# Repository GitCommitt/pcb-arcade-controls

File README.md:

# README: pcb-arcade-controls

# Planning: 
**Periode:** November 2026 t/m januari 2027

---

### Sprint 0
* **Periode:** 16 nov t/m 20 nov 2026
* **Taken:** 
  * Onderzoek / start

### Sprint 1
* **Periode:** 23 nov t/m 4 dec 2026
* **Taken:** 
  * Stroomschema ontwerpen

### Sprint 2
* **Periode:** 7 dec t/m 18 dec 2026
* **Taken:** 
  * Printplaat ontwerpen
  * Printplaten bestellen

### Kerstvakantie
* **Periode:** 21 dec 2026 t/m 1 jan 2027
* **Status:** Geen sprint

### Sprint 3
* **Periode:** 4 jan t/m 15 jan 2027
* **Taken:** 
  * Firmware & software
  * Handleidingen & solderen

### Sprint 4
* **Periode:** 18 jan t/m 22 jan 2027
* **Taken:** 
  * Polishen
  * CGI's
    
## Onderzoek

Bij het onderzoek zijn we begonnen met de PDF lezen en belangerijke dingen opslaan. We hebben aan het begin van dit process een [video](https://www.youtube.com/watch?v=8WXpGTIbxlQ) gekeken hoe we het software tool KiCad moeten gebruiken in combinatie met de STM32F072CBT6 Microprocessor.

### Keuze pins

Daan en Bram zijn gaan onderzoeken welke pins er gebruikt kunnen worden op de processor en kijken hoe we uitkkomen met de aantal connecties die we hebben door de connectors. Samen zijn we er uit gekomen dat het handig is om een matrix te gebruiken voor de connector connections naar de processor. We waren in de [datasheet](https://www.lcsc.com/datasheet/C81720.pdf) gedoken. Hier ijn we op pagina 35 onder het kopje (Pinouts and pin descriptions) onder wij gebruiken de pin number (LQFP48). Heir hebben we de pins uitgezocht welke we kunnen gebruiken.

## Kicad

In Kicad zijn we begonnen bij het maken van een nieuwe file met de template [library](https://github.com/GitCommitt/pcb-arcade-controls/tree/main/library/scottokeebs-main/Extras/ScottoModules/STM32F072CBT6) van de repo [Scottokeebs](https://github.com/joe-scotto/scottokeebs). Daarna hebben we voor het maken van een 3d model de [library](https://github.com/GitCommitt/pcb-arcade-controls/tree/main/library/scottokeebs-main/Extras/ScottoKicad/symbols) toegevoed aan onze preferences. 14

## Pin Layout

Hieronder staan de pins die we gebruiken in het project. Hier hebben Daan en Fynn samen onderzocht.

### Matrix, Kolommen & Rijen
| Pin | Functie | MCU Pin |
| :--- | :--- | :--- |
| **14** | Col 0 | `PA4` |
| **15** | Col 1 | `PA5` |
| **16** | Col 2 | `PA6` |
| **17** | Col 3 | `PA7` |
| **18** | Col 4 | `PB0` |
| **19** | Col 5 | `PB1` |
| **20** | Col 6 | `PB2` |
| **21** | Col 7 | `PB10` |
| **22** | Row 0 | `PB11` |
| **25** | Row 1 | `PB12` |
| **26** | Row 2 | `PB13` |
| **27** | Row 3 | `PB14` |

### Power & GND
| Pin | Functie | MCU Pin |
| :--- | :--- | :--- |
| **1** | VBAT | `VBAT` |
| **9** | VDDA | `VDDA` |
| **24** | VDD1 | `VDD` |
| **36** | VDDIO2 | `VDDIO2` |
| **48** | VDD2 | `VDD` |
| **8** | GND | `VSSA` |
| **23** | GND | `VSS` |

### USB & Debugging
| Pin | Functie | MCU Pin |
| :--- | :--- | :--- |
| **32** | USB_D- | `PA11` |
| **33** | USB_D+ | `PA12` |
| **34** | A13 | `PA13` |
| **37** | A14 | `PA14` |

### Systeem & Overige I/O
| Pin | Functie | MCU Pin |
| :--- | :--- | :--- |
| **2** | C13 | `PC13` |
| **3** | C14 | `PC14` |
| **4** | C15 | `PC15` |
| **7** | NRST | `NRST` |
| **28** | B15 | `PB15` |
| **44** | BOOT0 | `BOOT0` |

# Connector type

**PCB Connector**

Daan heeft voor de [JST-XH Female](https://nl.rs-online.com/web/p/pcb-headers/8201554) connectors gekozen als connectie type. Daan heeft deze keuze gemaakt aangezien deze type connector makkelijk is om te gebruiken en super gebruiksvriendelijk is. Ook was een reden dat Daan deze connectie type heeft gekozen dat deze connectors makkelijk op het bord passen en niet veel plek in beslag nemen op de printplaat. De andere connectie type die Daan als optie had waren de [Screw Terminals](https://www.amazon.nl/-/en/50pcs-Terminal-Connectors-Terminals-2-54mm/dp/B07BVF8MD1). Het voordeel bij deze connector was vooral dat hij universal is dus elke soort kabel kan gebruikt worden op deze connector. Daan heeft alleen niet voor deze connector gekozen om de volgende redenen. De connectors nemen veel plek in beslag op de printplaat en de connectors niet gebruiksvriendlijk aangezien je voor het veranderen van de kabel een schroevendraaier nodig heb.

**Kabel Connector**

We gaan voor de kabel connectors aan de pcb kant de [JST XH-2 Male](https://www.electrokit.com/en/batterisladd-jst-xh-2-pol-300mm) connectors gebruiken. Deze connectors passen perfect in de female connectors van de pcb. Als deze twee connectors zijn gekoppeld zijn ze moeilijk uit te halen en zullen ze dus niet uitvallen tijdens het gebruik. 

Aan de ardcade button kant van de kabel gaan we de [Quick-Connect](https://www.arcadewinkel.nl/en/wiring-connectors/connectors/quick-connector-2-8mm-110-inch-crimp-model-10pcs) connectors gebruiken aangezien deze makkelijk hot swapable zijn met de arcade buttons en dus ook heel gebruiksvriendelijk zijn voor de gebruikers als er word gewisseld van buttons.

De kabel die het uiteindelijk gaan worden zijn de [JST XH male / Quick-Connect Wires](https://www.amazon.nl/SJ-JX-Connectors-Controller-Accessories/dp/B08C2CLMJ5?th=1). Dit omdat deze het beste bij onze keuzes het beste passen en gaan werken in ons ontwerp.

## Matrix

Wij gaan een matrix gebruiken in ons prinplaat ontwerp, aangezien dit super handig en overzichtelijk is voor het pin gebruik van de pins op de processor. De matrix houd in dat de data en ground pins van de connectors worden samengevoegd zogeheten een matrix. Hierdoor hebben we inplaats van 24 pins maar 10 pins nodig. De verhouding van de matrix is 4 x 6 dat zijn dus 4 rows en 6 columns. Hierdoor hebben wij dus meer mogelijkheden om andere dingen toe te voegen zoals een led strip of andere componenten.

# Process

We zijn begonnen als een team met het bedenken van een strak plan om dit project zo goed en het soepelst mogelijk kan laten verlopen. We zijn eerst begonnen met de verdeling van de taken. In de PCB ontwerp periode zijn de volgende taken verdeelt. Fynn, Nathan en Kevin hebben de taken gekregen van het PCB ontwerp te creeren en dan ook gelijk in Kicad te verwerken. Daan en Bram hebben de taak gekregen om te kijken wat de beste opties zijn voor het gebruik van de pins. Hiermee word bedoeld van welke pins op de processor gebruikt worden voor data zodat het knoppen en joysticks goed gaan comminuceren met de processor. 

## Sprint 0 [↗️](https://github.com/GitCommitt/pcb-arcade-controls/tree/main/attachments/sprints/sprint-0)

### Doelen

...

### Aanpak
We hebben als eerst met het gehele team gekeken naar hoe het programma Kicad in elkaar zit en hoe we dit kunnen gaan gebruiken om de PCB uiteindelijk te kunnen ontwerpen. Er is ook een vergadering plaatsgevonden met het team waarbij we alles wat we hebben bij elkaar hebben gelegd om op die manier te meten waar we in het process staan. Wij hebben hiervoor ook ene duidelijke [planning](https://github.com/GitCommitt/pcb-arcade-controls/blob/main/README.md#planning) gemaakt voor wanneer welke taak afgerond moet zijn zodat we goed op schema blijven liggen. 

Samen met z'n allen is er een design ontworpen hoe het schema er op dit moment uit ziet ([Bekijk](https://github.com/GitCommitt/pcb-arcade-controls/blob/main/attachments/sprints/sprint-0/schema.png)). Hier zijn de PCB ontwerpers bezig geweest met het bouwen van de basis, dus er is op het schema te zien dat de benodigde connectors, processor, bootloaderknop en usb c port zijn toegevoegd. Later in het process/andere sprints zal er waarschijnlijk gebruik worden gemaakt van een matrix waardoor er nog meer connectors aangesloten kunnen worden en er daardoor meer controls zijn.

Het schema is ook al verwerkt in een visuele printplaat ontwerp ([Bekijk](https://github.com/GitCommitt/pcb-arcade-controls/blob/main/attachments/sprints/sprint-0/pcb.png)). Op dit ontwerp is te zien dat we 24 inputconnectoren gebruiken die we later gaan vervangen voor nieuwe connectors. Dat zijn de [JST-XH connectors](https://nl.rs-online.com/web/p/pcb-headers/8201554). Ook is er op de printplaat al nagedacht over hoe de printplaat gemonteerd kan worden aan een spelkast of ander iets. Hiervoor zijn 4 montagegaten van 10 mm gemaakt in de printplaat en worden waarschijnlijk later in het process smaller gemaakt zodat ze perfect bevestigd kunnen worden met een schroefjes. De processor, bootloaderknop en usb-c aansluiting zijn op dit ontwerp mogelijk op andere plekken dan ze op het eindproduct zouden zitten.

We hebben een presentatie gemaakt die deze sprint samenvat in 5 dia's ([Bekijk](https://github.com/GitCommitt/pcb-arcade-controls/blob/main/attachments/sprints/sprint-0/Presentatie%20sprint0.pptx)). Dit hebben we gepresenteerd en hebben we ook [feedback](https://github.com/GitCommitt/pcb-arcade-controls/blob/main/attachments/sprints/sprint-0/Resultaatfeedback%20presentative.txt) op gekregen en verwerkt.

## Sprint 1 [↗️](https://github.com/GitCommitt/pcb-arcade-controls/tree/main/attachments/sprints/sprint-1)

### Doelen [↗️](https://github.com/GitCommitt/pcb-arcade-controls/blob/main/attachments/sprints/sprint-1/Doel-sprint%201.docx)
Voor sprint 1 willen we ervoor zorgen dat we meer te weten komen hoe we moeten designen in kicad en hoe we alles kunnen toevoegen, zoals connectoren zoeken, processor importeren uit een bestaand project van andere. Ook moet er een begin gemaakt worden in kicad. De basis staat. Onder de basis valt uiteraard het ontwerpen van de pcb. 

De printplaat moet de volgende eisen hebben gehaald aan het einde van de week. De eerste eis is dat er een pcb moet staan die op maat is van de uiteindelijke printplaat. Hierdoor kunnen we zien hoeveel ruimte we hebben om te werken met de componenten die later worden toevoegt. De volgende eis is dat we de processor moeten vinden en die ook toevoegen in het project en uiteindelijk ook op die printplaat laat zetten. Hierbij hoort ook de bootknop, deze is cruciaal omdat door deze knop kunnen we firmware gaan zetten op de processor en het ook werkend kunnen laten maken. Ook moet de USB C port aanwezig zijn in het schematic en ook al op de printplaat fysiek zit. 

### Aanpak

Kevin is begonnen met het onderzoeken van hoe er samen in 1 KiCad bestand gewerkt kan worden zonder dat het elkaar constant over overschrijft. Dit is onderzocht en er kwam een stappenlijst uit. Het volgende is gedaan om dit probleem op te lossen: in KiCad is bij de voorkeuren git versie beheer ingeschakeld. Hierdoor overschrijven de bestanden niet meer waardoor er nu met meerdere personen aan 1 bestand gewerkt kan worden. Kevin heeft dit gedaan en werd hierbij geholpen door Daan, Nathan en Fynn.

Daan en Bram hebben ook het onderzoek gestart naar het kijken welke ADC connecties gebruikt kunnen worden van de processor voor de data en de ground connecties van de buttons ([Bekijk](https://github.com/GitCommitt/pcb-arcade-controls/blob/main/attachments/sprints/sprint-1/PINoutSchematic.txt)).

Het PCB ontwerp en de schematic worden nu aangepast en worden de temporary pins die nu gebruikt worden door de buttons opnieuw aan een pin gezet. Er word gewerkt aan het erin zetten van de processor op de pcb aangezien die nu niet word weergegeven bij de pcb. Nathan heeft de connectors toegevoegd en dus zijn de connectors die daadwerkelijk gebruikt gaan worden zichtbaar op de [pcb](https://github.com/GitCommitt/pcb-arcade-controls/blob/main/attachments/sprints/sprint-1/pcb.png). Hierdoor is er een beter zicht over hoe de pin lay-out eruit gaat zien en hoe de connectors op de pcb komen. [De pin layout](https://github.com/GitCommitt/pcb-arcade-controls/blob/main/attachments/sprints/sprint-1/PINoutSchematic.txt) is ook gecreerd waardoor er nu duidelijk gemaakt waar de pins heen gaan op de processor.

Kevin heeft de processor toegevoegd aan het [pcb design](https://github.com/GitCommitt/pcb-arcade-controls/blob/main/attachments/sprints/sprint-1/pcb-2.png) en deze is nu zichtbaar. De pins van de connectors moeten nog verbonden worden aan de processor alleen staat hij er voor nu wel alvast op de pcb en kunnen deze later aan elkaar verbonden worden voor een beter zicht op hoe de pcb gaat werken. De processor is uit de KiCad library gehaald en er was dus geen externe footprint voor nodig waardoor het ook makkelijker maakt voor op GitHub te zetten en samen te werken. 

Fynn heeft een nieuw [schematic](https://github.com/GitCommitt/pcb-arcade-controls/blob/main/attachments/sprints/sprint-1/schematic.png) gemaakt voor de connectors. Nu is er te vinden welke connectors bij welke column en row horen. hierdoor is het makkelijk te achterhalen welke connector waar heen moet. Ook zijn er nieuwe labels toegevoegd zoals player-1-button-1 etc etc. Ook is er toegevoegd in de [schematic](https://github.com/GitCommitt/pcb-arcade-controls/blob/main/attachments/sprints/sprint-1/schematic.png) welke diodes Fynn gebruikt voor de matrix. Op de prinplaat zijn ondertussen nieuwe [traces](https://github.com/GitCommitt/pcb-arcade-controls/blob/main/attachments/sprints/sprint-1/pcb-3.png) gelegd dat is op de fotos te zien van het 3d model.

Nathan heeft gewerkt aan het de gaten die in de printplaat komen. Hij is ervoor gaan zorgen dat hij bestel ready word. Hierdoor kunnen we uiteindelijk zelf de componenten gaan solderen aangezien het onnodig is om elke component erop te laten solderen door de fabriek. Alleen de capacitors en de MCU (processor) is blijven zitten aangezien deze componenten te klein zijn om die met de hand te solderen ([Bekijk](https://github.com/GitCommitt/pcb-arcade-controls/blob/main/attachments/sprints/sprint-1/pcb-holes.png)).

Kevin heeft de connecties van PA11 en PA12 die eerst MCU_D- en MCU_D+ waren nu veranderd naar USB_D- en USB_D+. Dit omdat dit overeenkomt met de USB C connector die we gebruiken op de printplaat. Dit is ook aangepast op het schematic [(Bekijk)](https://github.com/GitCommitt/pcb-arcade-controls/blob/main/attachments/sprints/sprint-1/schematic-usb_update.png). De traces van J3 naar U4 zijn beter geroute waardoor het nu er netter eruit ziet.

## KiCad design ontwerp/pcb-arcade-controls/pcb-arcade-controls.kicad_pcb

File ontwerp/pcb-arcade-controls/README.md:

# README: pcb-arcade-controls

**Onderzoek**
---

Bij het onderzoek zijn we begonnen met de PDF lezen en belangerijke dingen opslaan. We hebben aan het begin van dit process een [video](https://www.youtube.com/watch?v=8WXpGTIbxlQ) gekeken hoe we het software tool KiCad moeten gebruiken in combinatie met de STM32F072CBT6 Microprocessor.

## Kicad

In Kicad zijn we begonnen bij het maken van een nieuwe file met de template [library](https://github.com/GitCommitt/pcb-arcade-controls/tree/main/library/scottokeebs-main/Extras/ScottoModules/STM32F072CBT6) van de repo [Scottokeebs](https://github.com/joe-scotto/scottokeebs). Daarna hebben we voor het maken van een 3d model de [library](https://github.com/GitCommitt/pcb-arcade-controls/tree/main/library/scottokeebs-main/Extras/ScottoKicad/symbols) toegevoed aan onze preferences.

# Meeting 6 november 2026
- Externe power supply voor de led strip (omdat er anders dubbele volt op komt)

- ADC onderzoek nog doen (verder afmaken), (datasheets induiken, qmk adc (link naar tbos) adc pins zijn data pins maar niet allemaal)

-   pa0 tot pa15 ADC pins (dubbelchecken) qmk adc link checken

- page 35 datasheet (lscs.com/datasheet/C91720.pdf)

- form factor is LQFP48 

- ADC kan je het analog uitlezen

- op de sheet kijken welke pin werken

- niet naar de grotere versies kijken

- goed kijken welke ze hebben en welke je kan aansluiten (bij de datasheet)

- Eerst ADC pins klaar zetten en dan pas de rest

- Readme is voor alles

- Presentatie maken maandag 16 nov (daarbij de debriefing, taakverdeling, planning)

------

## Sprint meeting 0

Resultaat/feedback presentative:

- Alles ziet er goed uit ivm connectoren etc
- nu is het 0 punt en weten wat we moeten doen
- letten op documentatie, alles documenteren al is het iets kleins/simpel

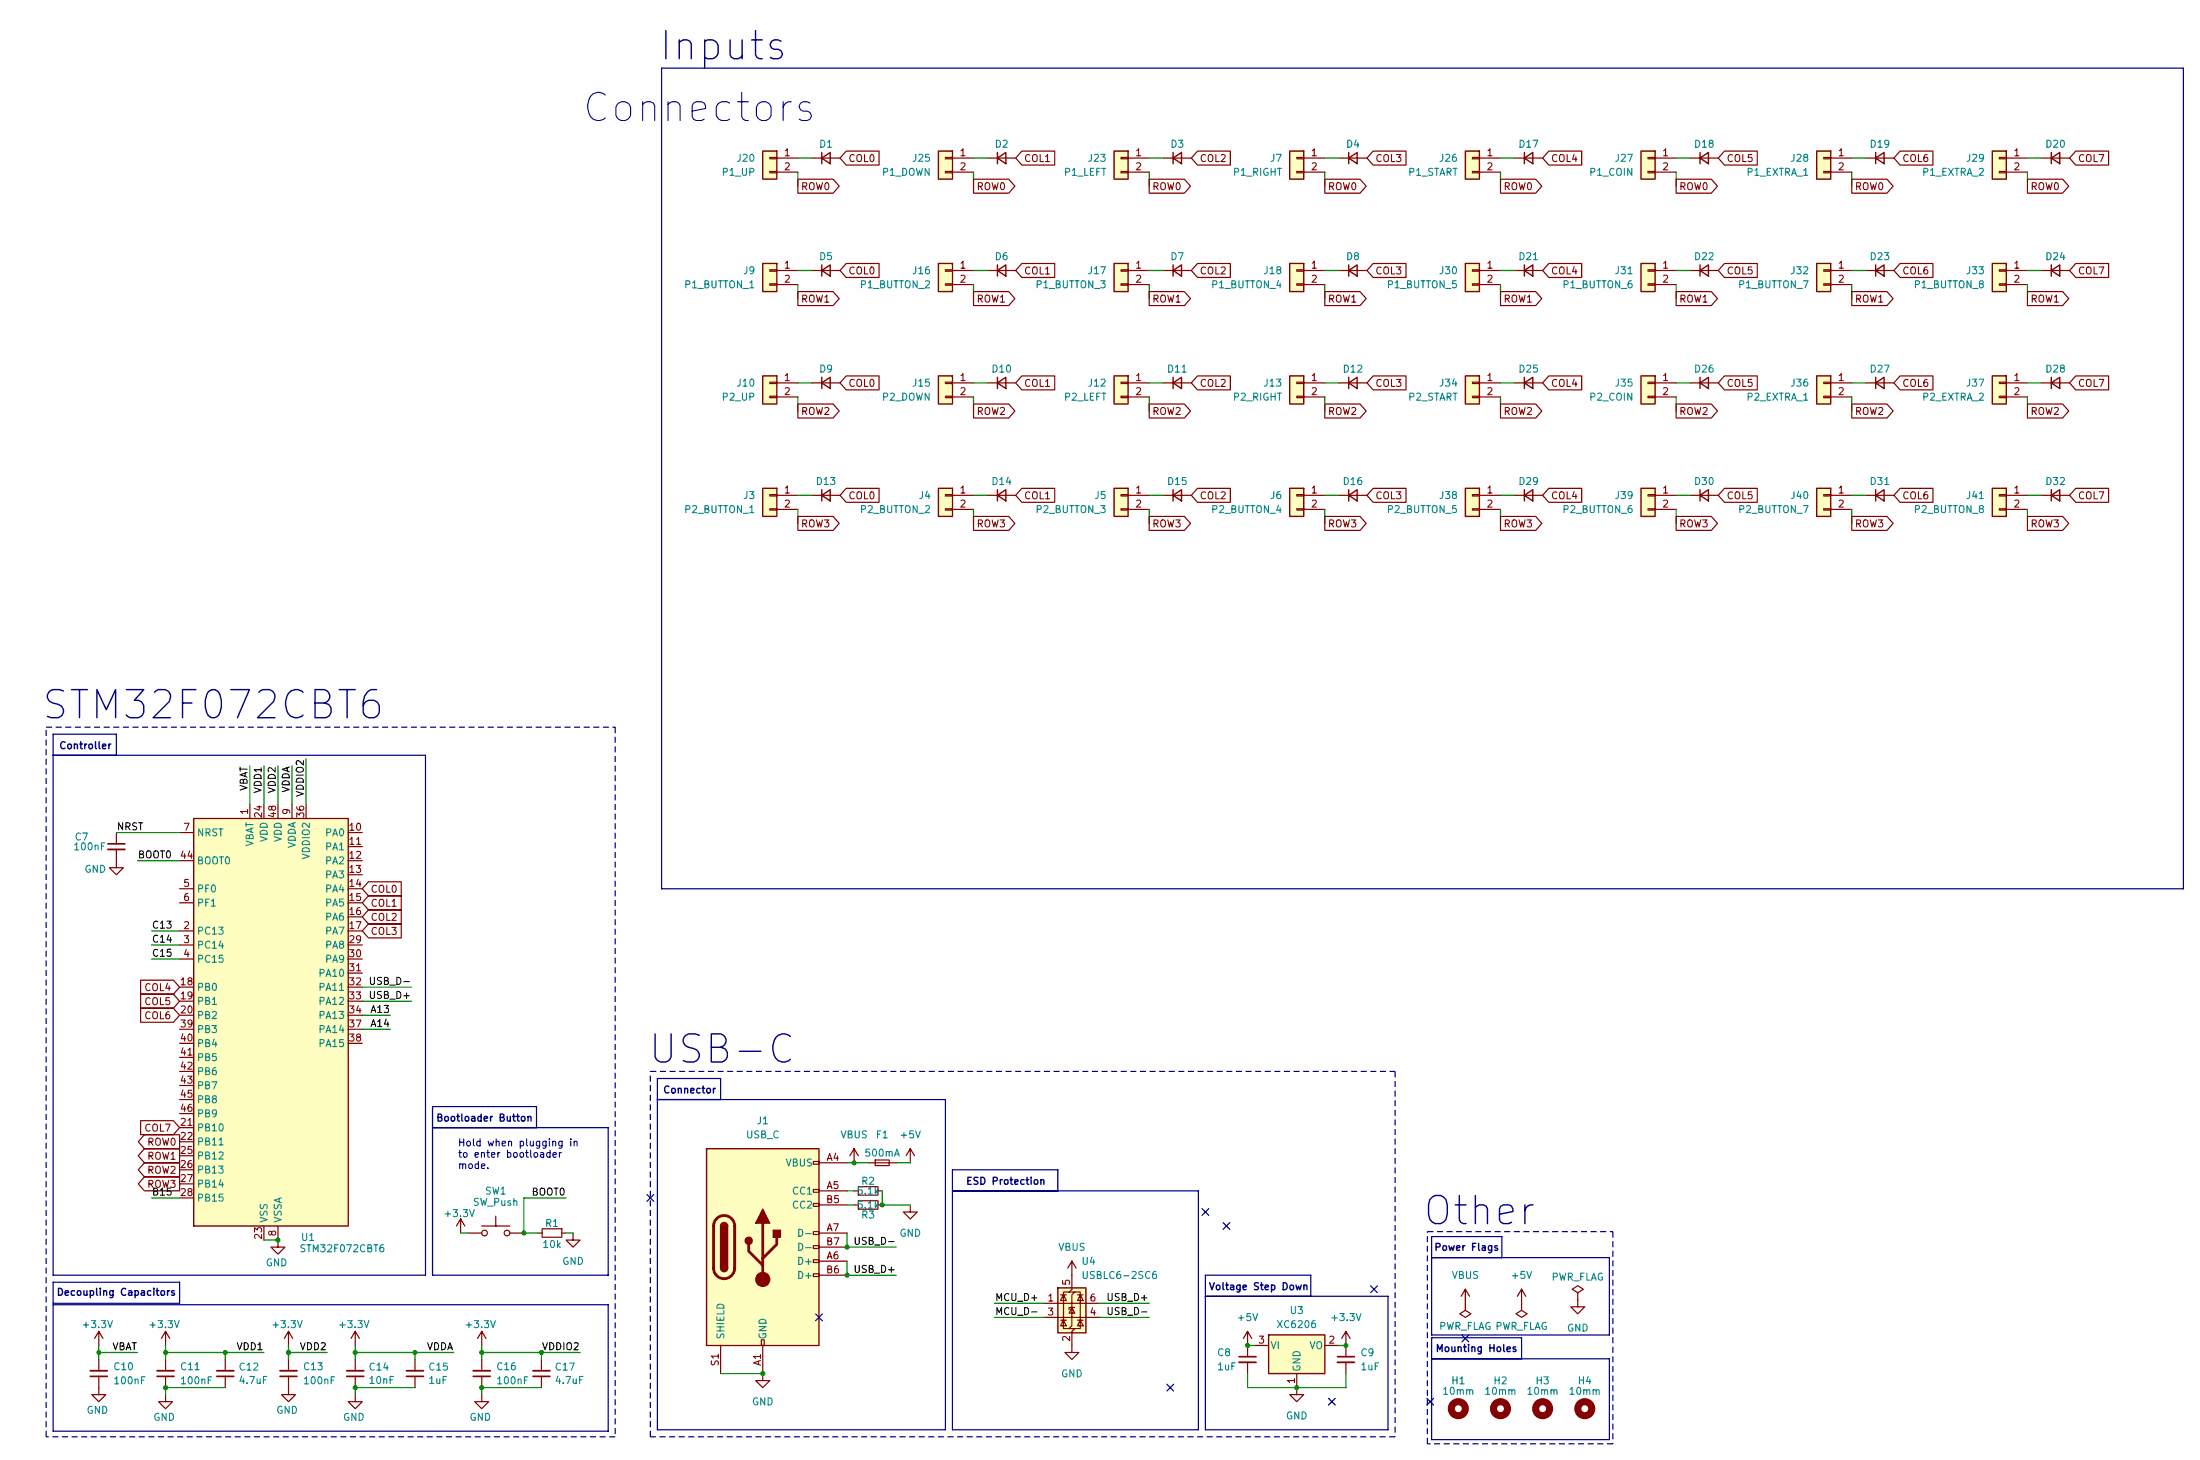
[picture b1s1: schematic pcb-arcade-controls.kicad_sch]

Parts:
C7: 100nF; C_Disc_D3.0mm_W1.6mm_P2.50mm; LCSC C307331
C8, C9: 1uF; C_Disc_D3.0mm_W1.6mm_P2.50mm; LCSC C52923
C10, C11, C13, C16: 100nF; C_Disc_D3.0mm_W1.6mm_P2.50mm; MPN CL05B104KB54PNC; LCSC C307331
C12, C17: 4.7uF; C_Disc_D3.0mm_W1.6mm_P2.50mm; MPN CL05A475MP5NRNC; LCSC C23733
C14: 10nF; C_Disc_D3.0mm_W1.6mm_P2.50mm; MPN CL05B103KB5NNNC; LCSC C15195
C15: 1uF; C_Disc_D3.0mm_W1.6mm_P2.50mm; MPN CL05A105KA5NQNC; LCSC C52923
D1, D2, D3, D4, D5, D6, D7, D8, D9, D10, D11, D12, D13, D14, D15, D16, D17, D18, D19, D20, D21, D22, D23, D24, D25, D26, D27, D28, D29, D30, D31, D32: 1N4148; D_DO-35_SOD27_P2.54mm_Vertical_AnodeUp
F1: 500mA; Fuse_Bourns_MF-RHT050; LCSC C210357
H1, H2, H3, H4: 10mm; MountingHole_10mm
J1: USB_C; USB_C_HRO_TYPE-C-31-M-12; LCSC C165948
J3: P2_BUTTON_1; JST_XH_B2B-XH-A_1x02_P2.50mm_Vertical
J4: P2_BUTTON_2; JST_XH_B2B-XH-A_1x02_P2.50mm_Vertical
J5: P2_BUTTON_3; JST_XH_B2B-XH-A_1x02_P2.50mm_Vertical
J6: P2_BUTTON_4; JST_XH_B2B-XH-A_1x02_P2.50mm_Vertical
J7: P1_RIGHT; JST_XH_B2B-XH-A_1x02_P2.50mm_Vertical
J9: P1_BUTTON_1; JST_XH_B2B-XH-A_1x02_P2.50mm_Vertical
J10: P2_UP; JST_XH_B2B-XH-A_1x02_P2.50mm_Vertical
J12: P2_LEFT; JST_XH_B2B-XH-A_1x02_P2.50mm_Vertical
J13: P2_RIGHT; JST_XH_B2B-XH-A_1x02_P2.50mm_Vertical
J15: P2_DOWN; JST_XH_B2B-XH-A_1x02_P2.50mm_Vertical
J16: P1_BUTTON_2; JST_XH_B2B-XH-A_1x02_P2.50mm_Vertical
J17: P1_BUTTON_3; JST_XH_B2B-XH-A_1x02_P2.50mm_Vertical
J18: P1_BUTTON_4; JST_XH_B2B-XH-A_1x02_P2.50mm_Vertical
J20: P1_UP; JST_XH_B2B-XH-A_1x02_P2.50mm_Vertical
J23: P1_LEFT; JST_XH_B2B-XH-A_1x02_P2.50mm_Vertical
J25: P1_DOWN; JST_XH_B2B-XH-A_1x02_P2.50mm_Vertical
J26: P1_START; JST_XH_B2B-XH-A_1x02_P2.50mm_Vertical
J27: P1_COIN; JST_XH_B2B-XH-A_1x02_P2.50mm_Vertical
J28: P1_EXTRA_1; JST_XH_B2B-XH-A_1x02_P2.50mm_Vertical
J29: P1_EXTRA_2; JST_XH_B2B-XH-A_1x02_P2.50mm_Vertical
J30: P1_BUTTON_5; JST_XH_B2B-XH-A_1x02_P2.50mm_Vertical
J31: P1_BUTTON_6; JST_XH_B2B-XH-A_1x02_P2.50mm_Vertical
J32: P1_BUTTON_7; JST_XH_B2B-XH-A_1x02_P2.50mm_Vertical
J33: P1_BUTTON_8; JST_XH_B2B-XH-A_1x02_P2.50mm_Vertical
J34: P2_START; JST_XH_B2B-XH-A_1x02_P2.50mm_Vertical
J35: P2_COIN; JST_XH_B2B-XH-A_1x02_P2.50mm_Vertical
J36: P2_EXTRA_1; JST_XH_B2B-XH-A_1x02_P2.50mm_Vertical
J37: P2_EXTRA_2; JST_XH_B2B-XH-A_1x02_P2.50mm_Vertical
J38: P2_BUTTON_5; JST_XH_B2B-XH-A_1x02_P2.50mm_Vertical
J39: P2_BUTTON_6; JST_XH_B2B-XH-A_1x02_P2.50mm_Vertical
J40: P2_BUTTON_7; JST_XH_B2B-XH-A_1x02_P2.50mm_Vertical
J41: P2_BUTTON_8; JST_XH_B2B-XH-A_1x02_P2.50mm_Vertical
R1: 10k; R_Axial_DIN0207_L6.3mm_D2.5mm_P2.54mm_Vertical; LCSC C25744
R2, R3: 5.1k; R_Axial_DIN0207_L6.3mm_D2.5mm_P2.54mm_Vertical; LCSC C25905
SW1: SW_Push; SW_PUSH_6mm; LCSC C115351
U1: STM32F072CBT6; Package_LQFP-48_7x7mm_P0.5; LCSC C81720
U3: XC6206; Voltage_SOT-23; LCSC C5446
U4: USBLC6-2SC6; ESD_SOT-23-6; LCSC C2827654

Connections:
+3.3V: C9.1, C10.2, C11.2, C12.2, C13.2, C14.2, C15.2, C16.2, C17.2, SW1.1, U1.1 (VBAT), U1.9 (VDDA), U1.24 (VDD), U1.36 (VDDIO2), U1.48 (VDD), U3.2 (VO)
+5V: C8.1, F1.2, U3.3 (VI)
/A13: U1.34 (PA13)
/A14: U1.37 (PA14)
/B15: U1.28 (PB15)
/BOOT0: R1.2, SW1.2, U1.44 (BOOT0)
/C13: U1.2 (PC13)
/C14: U1.3 (PC14)
/C15: U1.4 (PC15)
/NRST: C7.1, U1.7 (NRST)
COL0: D1.2 (A), D5.2 (A), D9.2 (A), D13.2 (A), U1.14 (PA4)
COL1: D2.2 (A), D6.2 (A), D10.2 (A), D14.2 (A), U1.15 (PA5)
COL2: D3.2 (A), D7.2 (A), D11.2 (A), D15.2 (A), U1.16 (PA6)
COL3: D4.2 (A), D8.2 (A), D12.2 (A), D16.2 (A), U1.17 (PA7)
COL4: D17.2 (A), D21.2 (A), D25.2 (A), D29.2 (A), U1.18 (PB0)
COL5: D18.2 (A), D22.2 (A), D26.2 (A), D30.2 (A), U1.19 (PB1)
COL6: D19.2 (A), D23.2 (A), D27.2 (A), D31.2 (A), U1.20 (PB2)
COL7: D20.2 (A), D24.2 (A), D28.2 (A), D32.2 (A), U1.21 (PB10)
GND: C7.2, C8.2, C9.2, C10.1, C11.1, C12.1, C13.1, C14.1, C15.1, C16.1, C17.1, J1.A1 (GND), J1.A12 (GND), J1.B1 (GND), J1.B12 (GND), J1.S1 (SHIELD), R1.1, R2.2, R3.2, U1.8 (VSSA), U1.23 (VSS), U1.35 (VSS), U1.47 (VSS), U3.1 (GND), U4.2 (GND)
unnamed: D1.1 (K), J20.1
unnamed: D2.1 (K), J25.1
unnamed: D3.1 (K), J23.1
unnamed: D4.1 (K), J7.1
unnamed: D5.1 (K), J9.1
unnamed: D6.1 (K), J16.1
unnamed: D7.1 (K), J17.1
unnamed: D8.1 (K), J18.1
unnamed: D9.1 (K), J10.1
unnamed: D10.1 (K), J15.1
unnamed: D11.1 (K), J12.1
unnamed: D12.1 (K), J13.1
unnamed: D13.1 (K), J3.1
unnamed: D14.1 (K), J4.1
unnamed: D15.1 (K), J5.1
unnamed: D16.1 (K), J6.1
unnamed: D17.1 (K), J26.1
unnamed: D18.1 (K), J27.1
unnamed: D19.1 (K), J28.1
unnamed: D20.1 (K), J29.1
unnamed: D21.1 (K), J30.1
unnamed: D22.1 (K), J31.1
unnamed: D23.1 (K), J32.1
unnamed: D24.1 (K), J33.1
unnamed: D25.1 (K), J34.1
unnamed: D26.1 (K), J35.1
unnamed: D27.1 (K), J36.1
unnamed: D28.1 (K), J37.1
unnamed: D29.1 (K), J38.1
unnamed: D30.1 (K), J39.1
unnamed: D31.1 (K), J40.1
unnamed: D32.1 (K), J41.1
unnamed: J1.A5 (CC1), R2.1
unnamed: J1.B5 (CC2), R3.1
ROW0: J7.2, J20.2, J23.2, J25.2, J26.2, J27.2, J28.2, J29.2, U1.22 (PB11)
ROW1: J9.2, J16.2, J17.2, J18.2, J30.2, J31.2, J32.2, J33.2, U1.25 (PB12)
ROW2: J10.2, J12.2, J13.2, J15.2, J34.2, J35.2, J36.2, J37.2, U1.26 (PB13)
ROW3: J3.2, J4.2, J5.2, J6.2, J38.2, J39.2, J40.2, J41.2, U1.27 (PB14)
VBUS: F1.1, J1.A4 (VBUS), J1.A9 (VBUS), J1.B4 (VBUS), J1.B9 (VBUS), U4.5 (VBUS)

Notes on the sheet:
STM32F072CBT6
USB-C
Mounting Holes
Decoupling Capacitors
Controller
ESD Protection
Power Flags
Voltage Step Down
Connectors
Other
Bootloader Button
Inputs
Connector
Hold when plugging in to enter bootloader mode.

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
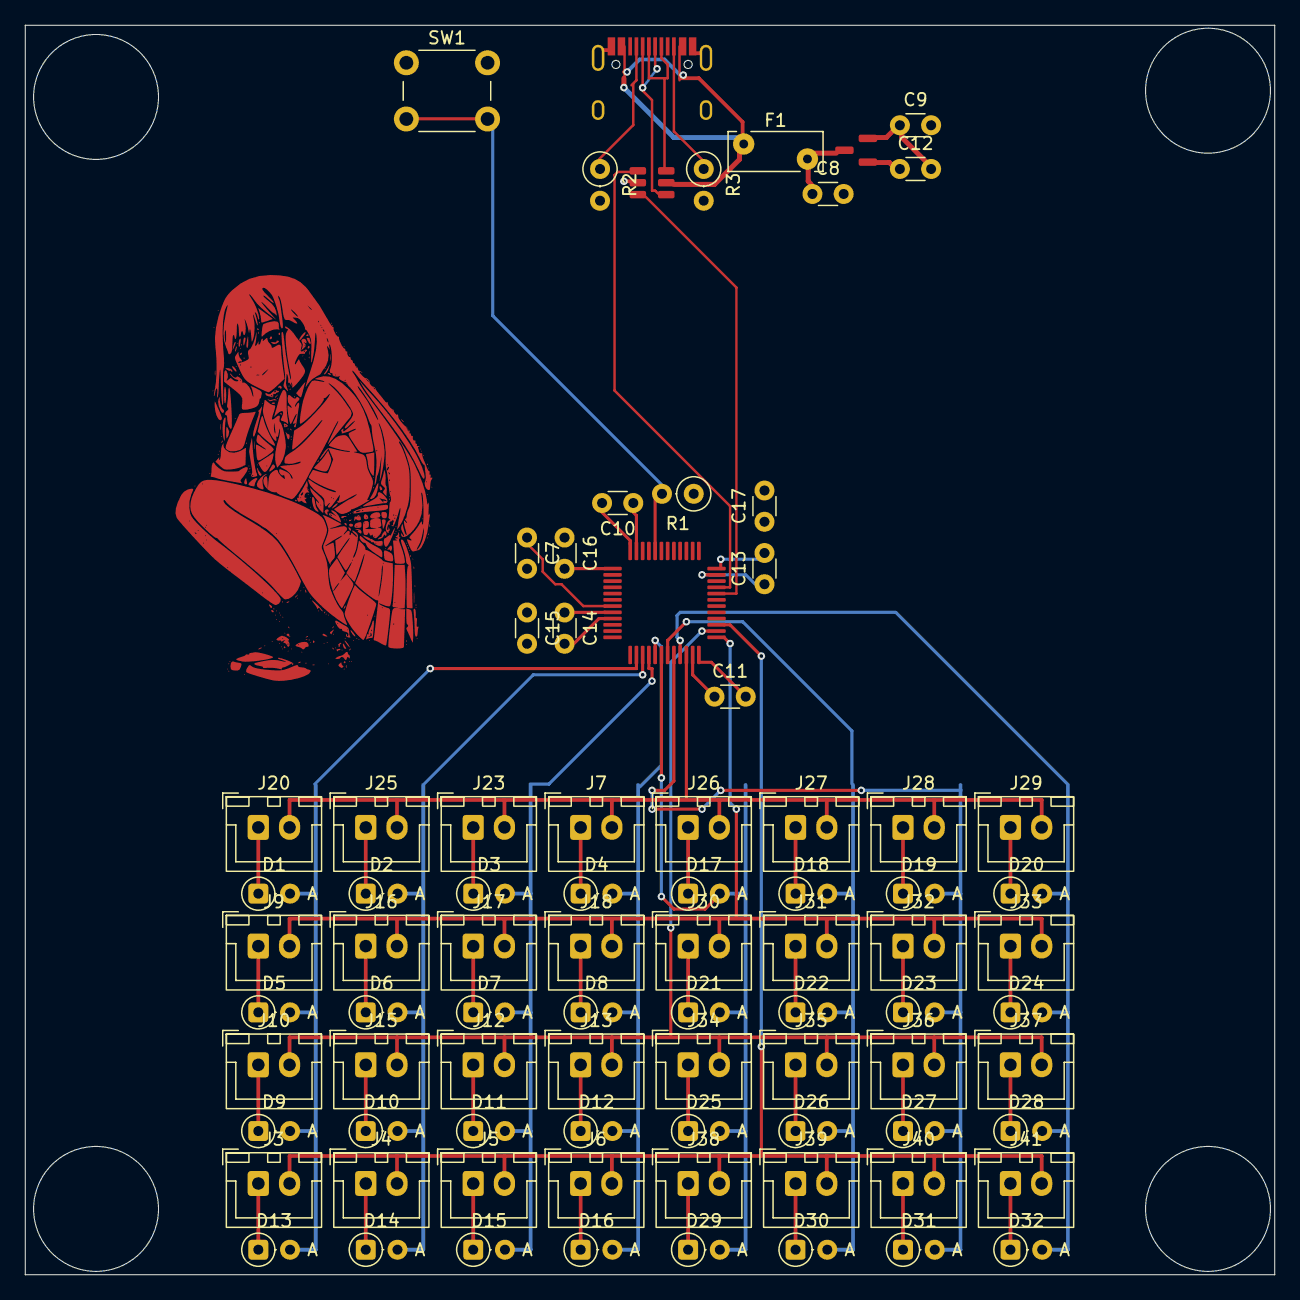
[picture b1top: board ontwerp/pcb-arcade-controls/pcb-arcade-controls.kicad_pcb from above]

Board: 4 copper layers, 100.0 x 100.0 mm, 88 parts (0 on the bottom side), 56 nets.

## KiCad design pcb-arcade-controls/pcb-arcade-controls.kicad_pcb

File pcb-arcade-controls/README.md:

# README: pcb-arcade-controls

**Onderzoek**
---

Bij het onderzoek zijn we begonnen met de PDF lezen en belangerijke dingen opslaan. We hebben aan het begin van dit process een [video](https://www.youtube.com/watch?v=8WXpGTIbxlQ) gekeken hoe we het software tool KiCad moeten gebruiken in combinatie met de STM32F072CBT6 Microprocessor.

## Kicad

In Kicad zijn we begonnen bij het maken van een nieuwe file met de template [library](https://github.com/GitCommitt/pcb-arcade-controls/tree/main/library/scottokeebs-main/Extras/ScottoModules/STM32F072CBT6) van de repo [Scottokeebs](https://github.com/joe-scotto/scottokeebs). Daarna hebben we voor het maken van een 3d model de [library](https://github.com/GitCommitt/pcb-arcade-controls/tree/main/library/scottokeebs-main/Extras/ScottoKicad/symbols) toegevoed aan onze preferences.

# Meeting 6 november 2026
- Externe power supply voor de led strip (omdat er anders dubbele volt op komt)

- ADC onderzoek nog doen (verder afmaken), (datasheets induiken, qmk adc (link naar tbos) adc pins zijn data pins maar niet allemaal

-   pa0 tot pa15 ADC pins (dubbelchecken) qmk adc link checken

- page 35 datasheet (lscs.com/datasheet/C91720.pdf)

- form factor is LQFP48 

- ADC kan je het analog uitlezen

- op de sheet kijken welke pin werken

- niet naar de grotere versies kijken

- goed kijken welke ze hebben en welke je kan aansluiten (bij de datasheet)

- Eerst ADC pins klaar zetten en dan pas de rest

- Readme is voor alles

- Presentatie maken maandag 16 nov (daarbij de debriefing, taakverdeling, planning)

------

## Sprint meeting 0

Resultaat/feedback presentative:

- Alles ziet er goed uit ivm connectoren etc
- nu is het 0 punt en weten wat we moeten doen
- letten op documentatie, alles documenteren al is het iets kleins/simpel

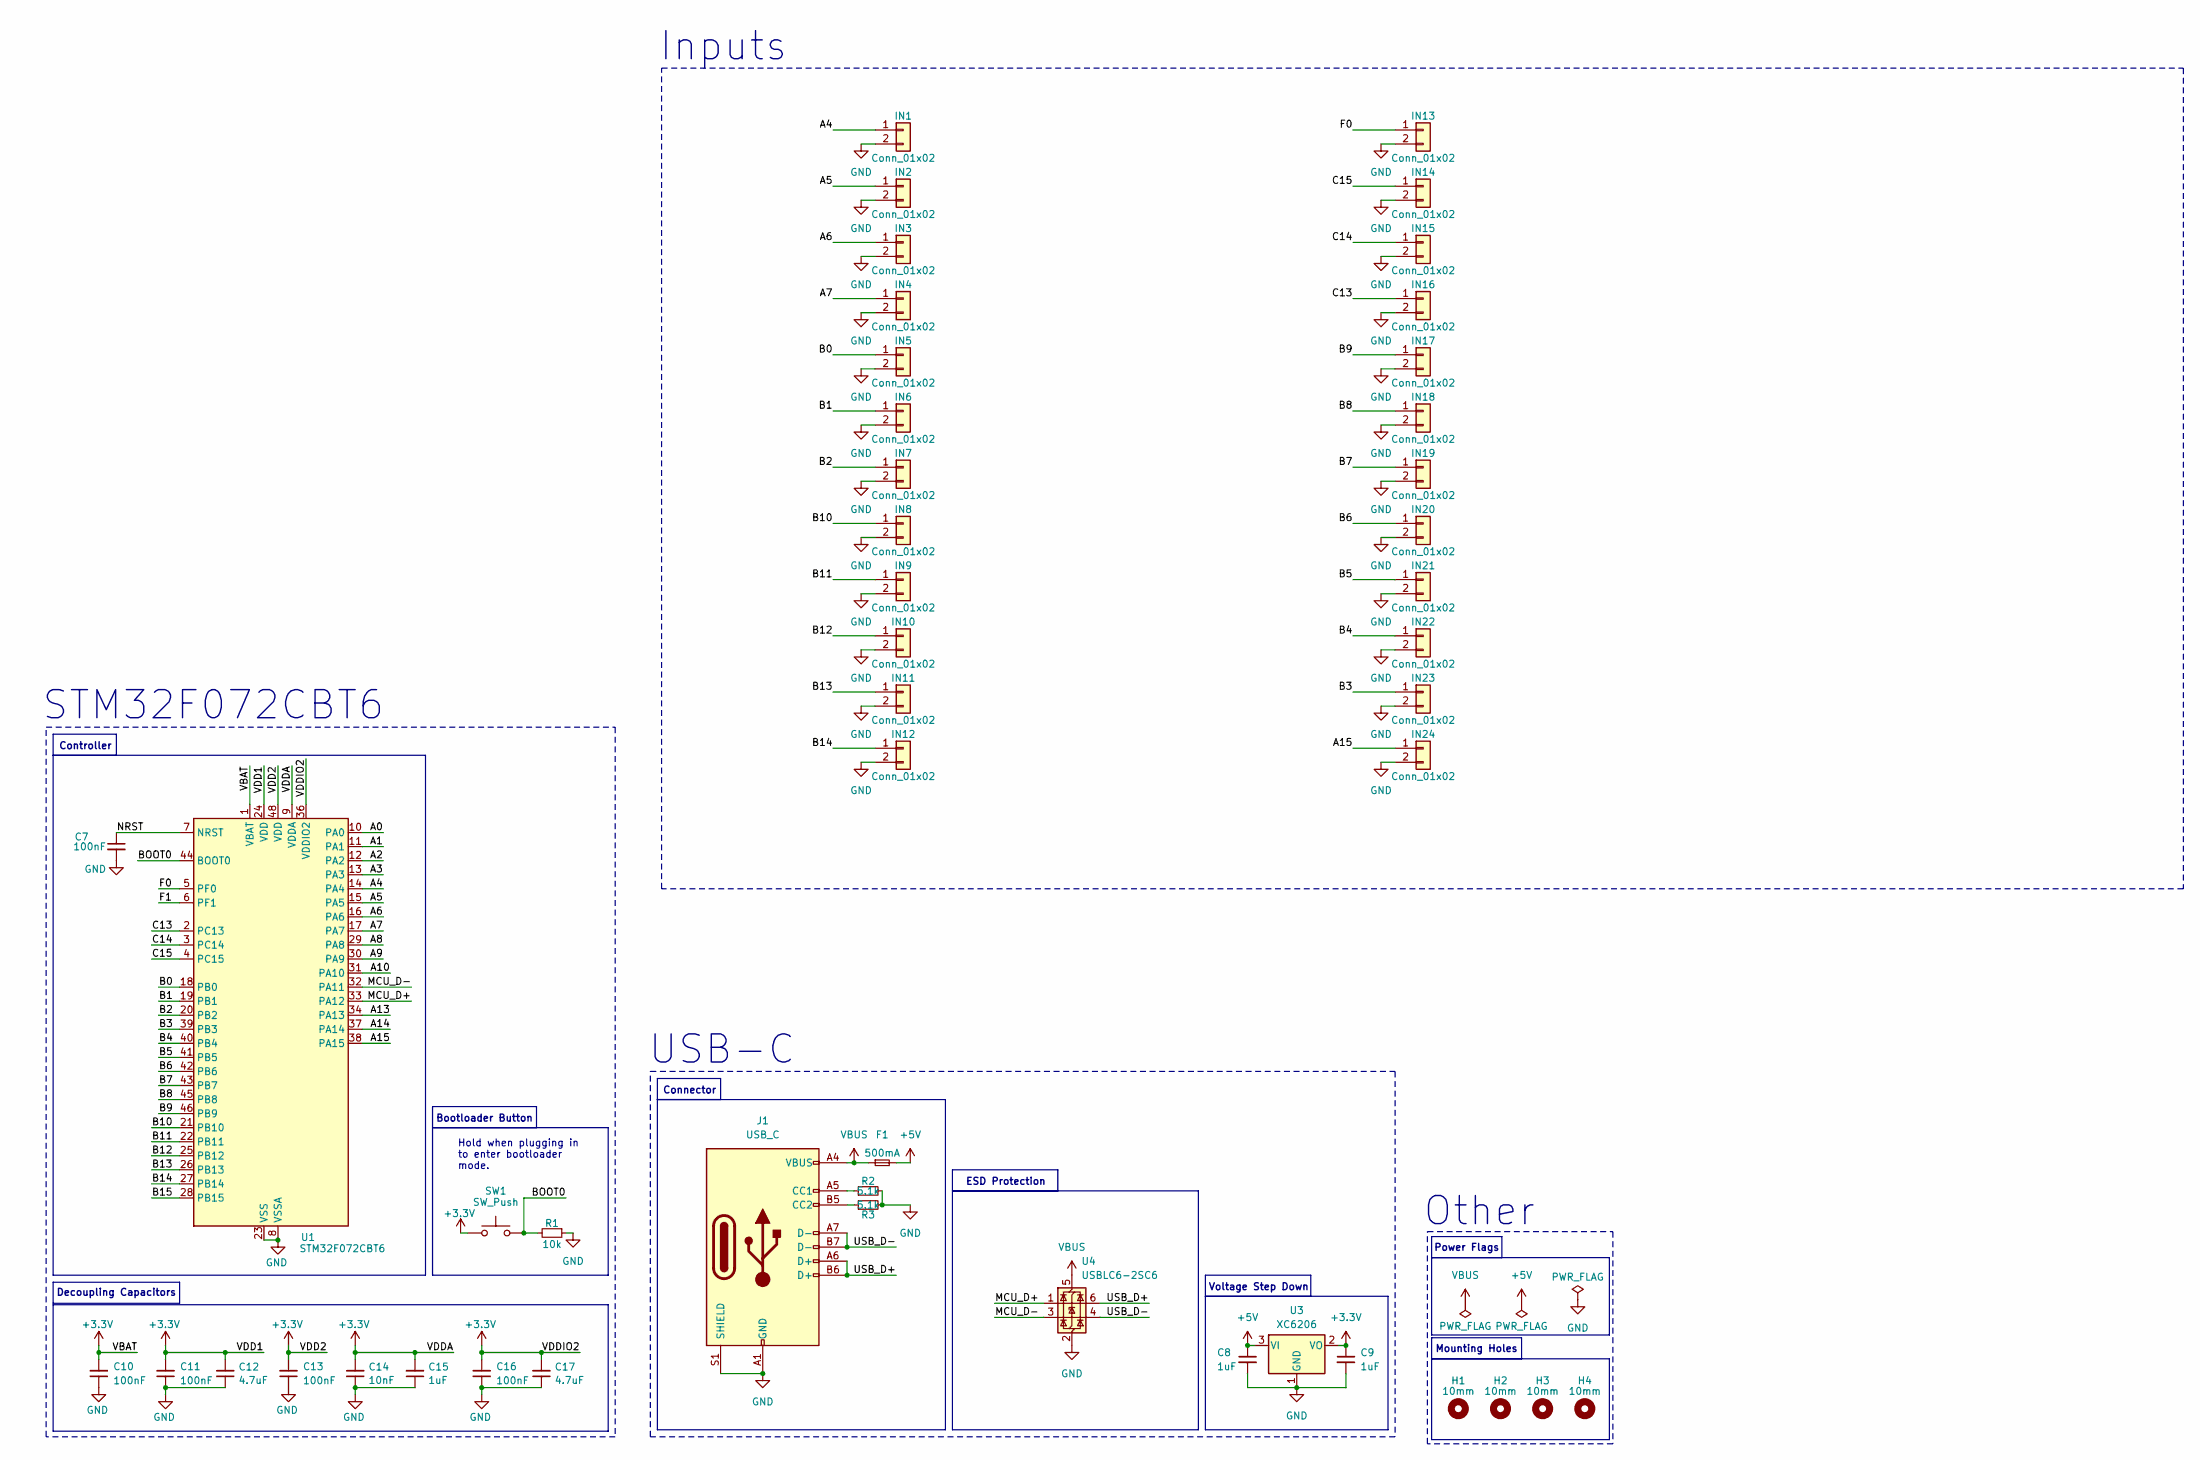
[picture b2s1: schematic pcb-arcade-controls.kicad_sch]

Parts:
C7: 100nF; Capacitor_0402; LCSC C307331
C8, C9: 1uF; Capacitor_0402; LCSC C52923
C10, C11, C13, C16: 100nF; Capacitor_0402; MPN CL05B104KB54PNC; LCSC C307331
C12, C17: 4.7uF; Capacitor_0402; MPN CL05A475MP5NRNC; LCSC C23733
C14: 10nF; Capacitor_0402; MPN CL05B103KB5NNNC; LCSC C15195
C15: 1uF; Capacitor_0402; MPN CL05A105KA5NQNC; LCSC C52923
F1: 500mA; Fuse_0603; LCSC C210357
H1, H2, H3, H4: 10mm; MountingHole_10mm
IN1, IN2, IN3, IN4, IN5, IN6, IN7, IN8, IN9, IN10, IN11, IN12, IN13, IN14, IN15, IN16, IN17, IN18, IN19, IN20, IN21, IN22, IN23, IN24: Conn_01x02; PinHeader_1x02_P2.54mm_Vertical
J1: USB_C; USB_C_HRO_TYPE-C-31-M-12; LCSC C165948
R1: 10k; Resistor_0402; LCSC C25744
R2, R3: 5.1k; Resistor_0402; LCSC C25905
SW1: SW_Push; Button_TL3342; LCSC C115351
U1: STM32F072CBT6; Package_LQFP-48_7x7mm_P0.5; LCSC C81720
U3: XC6206; Voltage_SOT-23; LCSC C5446
U4: USBLC6-2SC6; ESD_SOT-23-6; LCSC C2827654

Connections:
+3.3V: C9.1, C10.2, C11.2, C12.2, C13.2, C14.2, C15.2, C16.2, C17.2, SW1.1, U1.1 (VBAT), U1.9 (VDDA), U1.24 (VDD), U1.36 (VDDIO2), U1.48 (VDD), U3.2 (VO)
+5V: C8.1, F1.2, U3.3 (VI)
/A0: U1.10 (PA0)
/A1: U1.11 (PA1)
/A2: U1.12 (PA2)
/A3: U1.13 (PA3)
/A4: IN1.1, U1.14 (PA4)
/A5: IN2.1, U1.15 (PA5)
/A6: IN3.1, U1.16 (PA6)
/A7: IN4.1, U1.17 (PA7)
/A8: U1.29 (PA8)
/A9: U1.30 (PA9)
/A10: U1.31 (PA10)
/A13: U1.34 (PA13)
/A14: U1.37 (PA14)
/A15: IN24.1, U1.38 (PA15)
/B0: IN5.1, U1.18 (PB0)
/B1: IN6.1, U1.19 (PB1)
/B2: IN7.1, U1.20 (PB2)
/B3: IN23.1, U1.39 (PB3)
/B4: IN22.1, U1.40 (PB4)
/B5: IN21.1, U1.41 (PB5)
/B6: IN20.1, U1.42 (PB6)
/B7: IN19.1, U1.43 (PB7)
/B8: IN18.1, U1.45 (PB8)
/B9: IN17.1, U1.46 (PB9)
/B10: IN8.1, U1.21 (PB10)
/B11: IN9.1, U1.22 (PB11)
/B12: IN10.1, U1.25 (PB12)
/B13: IN11.1, U1.26 (PB13)
/B14: IN12.1, U1.27 (PB14)
/B15: U1.28 (PB15)
/BOOT0: R1.2, SW1.2, U1.44 (BOOT0)
/C13: IN16.1, U1.2 (PC13)
/C14: IN15.1, U1.3 (PC14)
/C15: IN14.1, U1.4 (PC15)
/F0: IN13.1, U1.5 (PF0)
/F1: U1.6 (PF1)
/MCU_D+: U1.33 (PA12), U4.1 (I/O1)
/MCU_D-: U1.32 (PA11), U4.3 (I/O2)
/NRST: C7.1, U1.7 (NRST)
/USB_D+: J1.A6 (D+), J1.B6 (D+), U4.6 (I/O1)
/USB_D-: J1.A7 (D-), J1.B7 (D-), U4.4 (I/O2)
GND: C7.2, C8.2, C9.2, C10.1, C11.1, C12.1, C13.1, C14.1, C15.1, C16.1, C17.1, IN1.2, IN2.2, IN3.2, IN4.2, IN5.2, IN6.2, IN7.2, IN8.2, IN9.2, IN10.2, IN11.2, IN12.2, IN13.2, IN14.2, IN15.2, IN16.2, IN17.2, IN18.2, IN19.2, IN20.2, IN21.2, IN22.2, IN23.2, IN24.2, J1.A1 (GND), J1.A12 (GND), J1.B1 (GND), J1.B12 (GND), J1.S1 (SHIELD), R1.1, R2.2, R3.2, U1.8 (VSSA), U1.23 (VSS), U1.35 (VSS), U1.47 (VSS), U3.1 (GND), U4.2 (GND)
unnamed: J1.A5 (CC1), R2.1
unnamed: J1.B5 (CC2), R3.1
VBUS: F1.1, J1.A4 (VBUS), J1.A9 (VBUS), J1.B4 (VBUS), J1.B9 (VBUS), U4.5 (VBUS)

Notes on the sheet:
STM32F072CBT6
USB-C
Mounting Holes
Decoupling Capacitors
Controller
ESD Protection
Power Flags
Voltage Step Down
Other
Bootloader Button
Inputs
Connector
Hold when plugging in to enter bootloader mode.

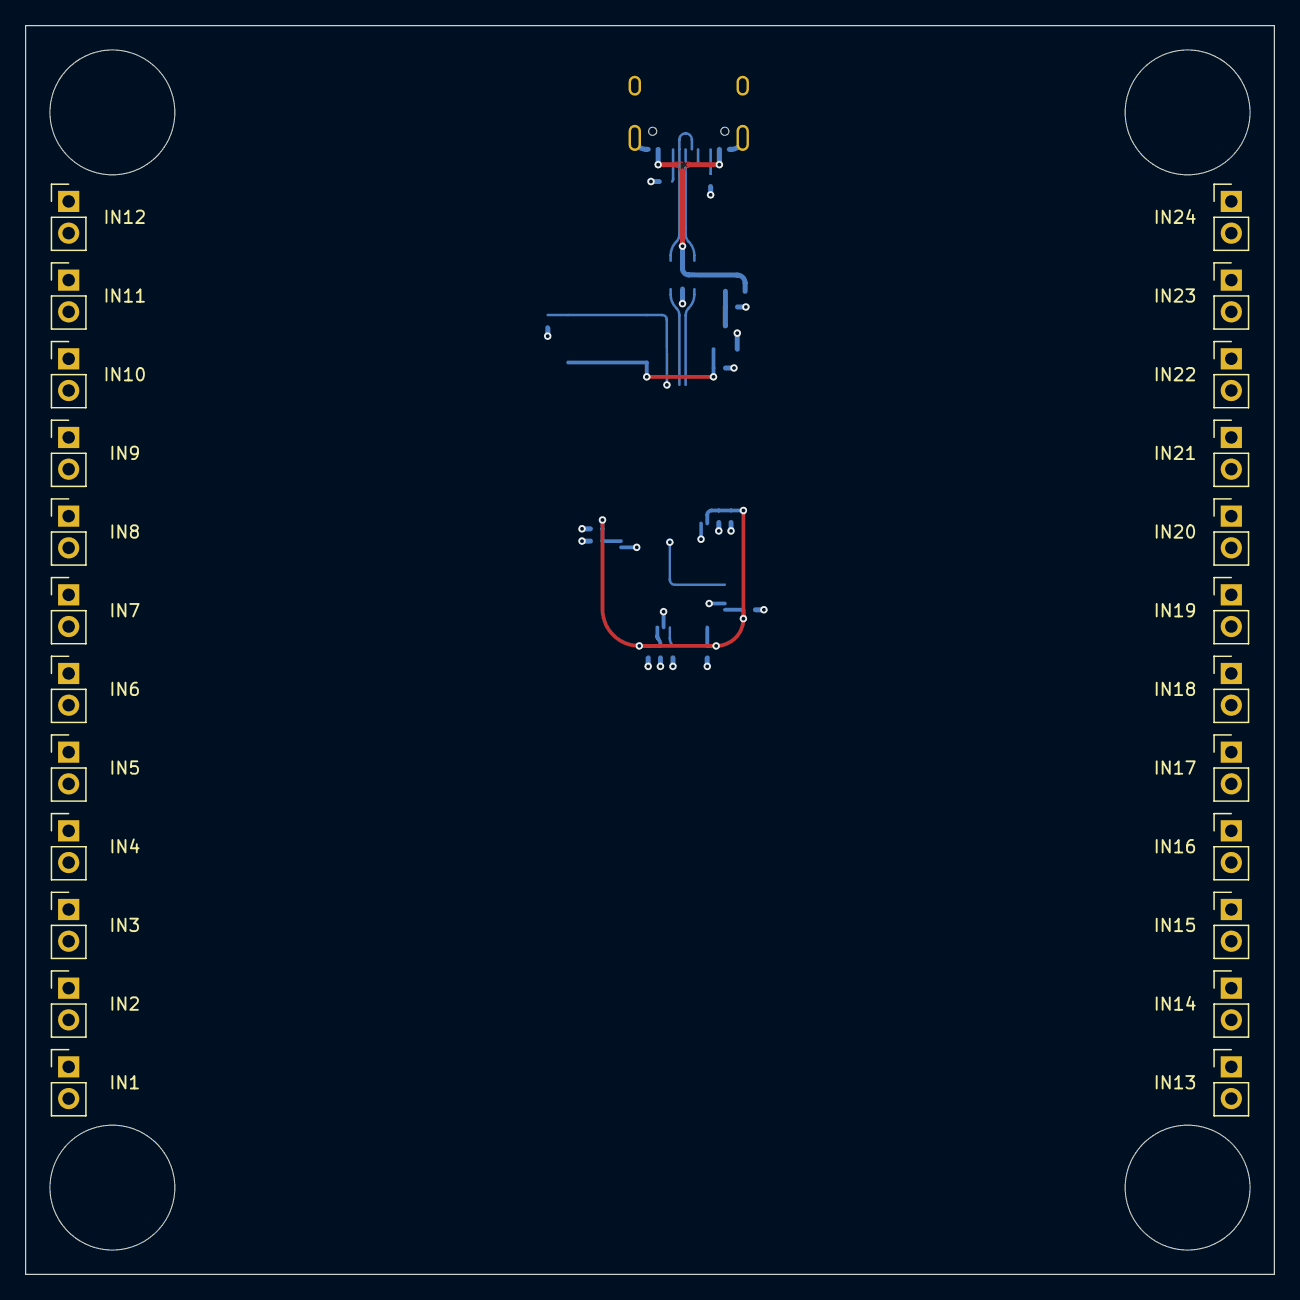
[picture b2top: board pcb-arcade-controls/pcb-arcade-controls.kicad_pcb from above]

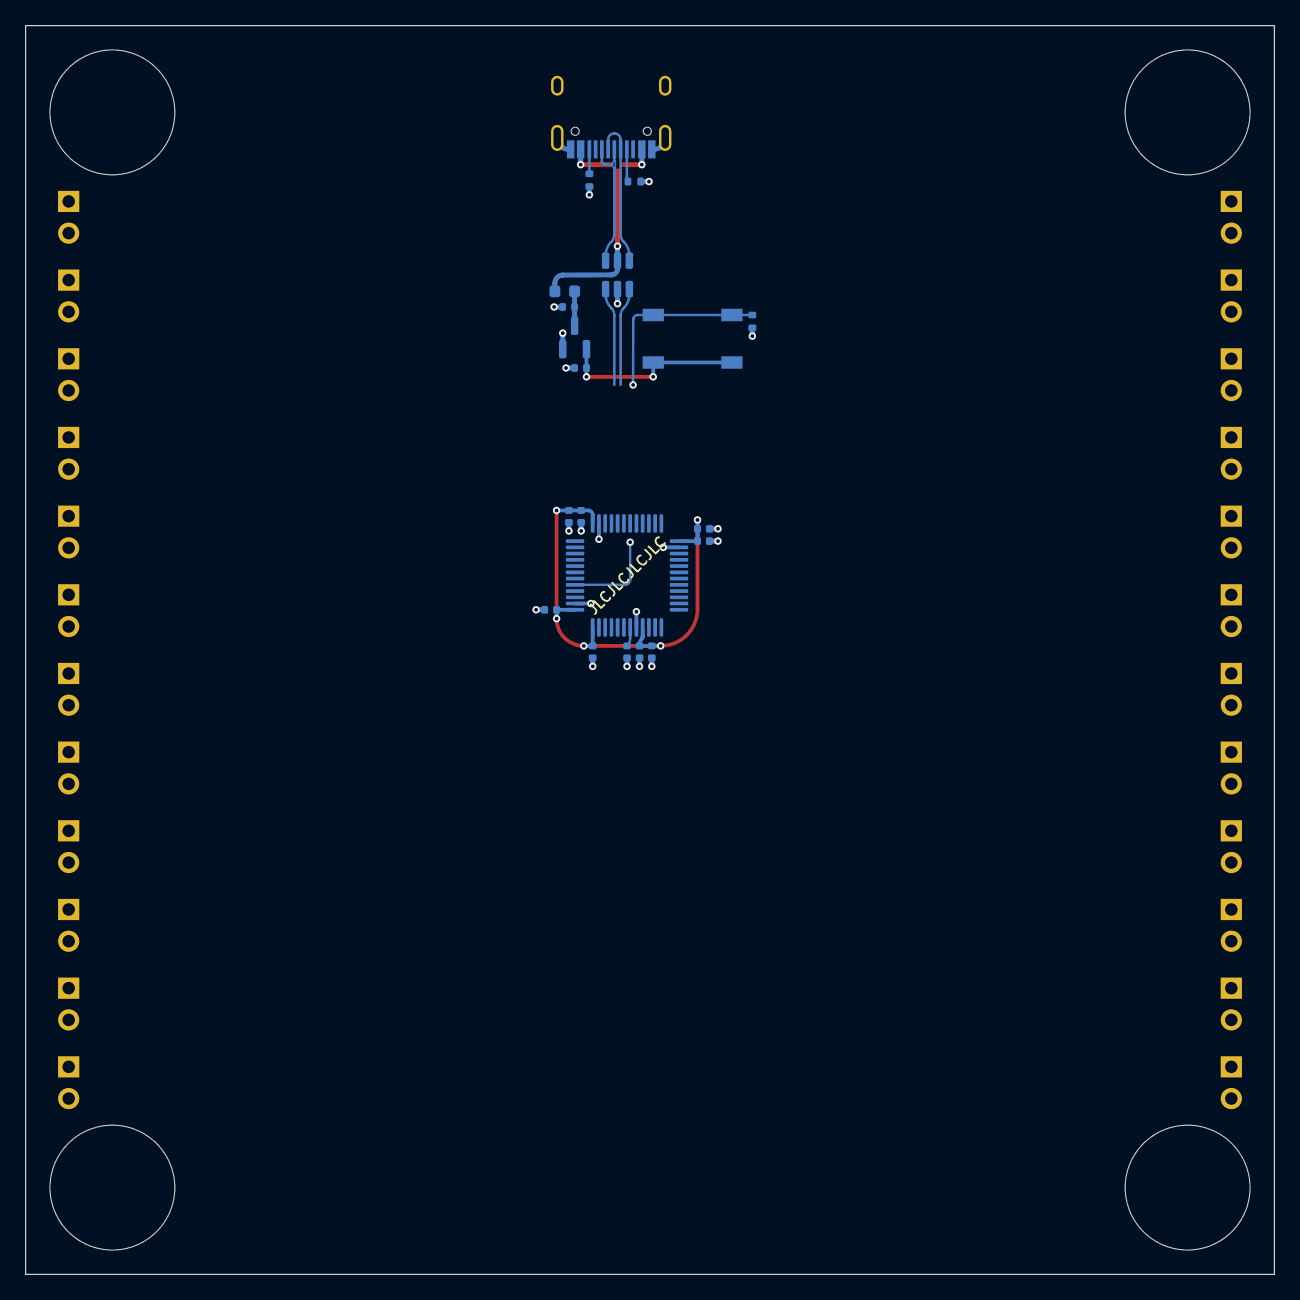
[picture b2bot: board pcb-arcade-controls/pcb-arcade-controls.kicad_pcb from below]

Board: 4 copper layers, 100.0 x 100.0 mm, 48 parts (20 on the bottom side), 36 nets.
